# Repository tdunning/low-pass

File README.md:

# 5th Order Chebyshev Low Pass Filter

This directory contains the design for a low-pass filter designed with
anti-aliasing in mind and laid out to avoid inadvertent coupling.

A typical use might be on the output of a direct synthesis chip such
as the AD9851. The DAC in an AD9851 is clocked at 180Ms/s which gives
rise to sampling noise at 180MHz. In addition, if you are generating a
waveform at frequency $f$, there will be an image in frequency space
of that output at $180MHz - f$. This filter is intended to suppress
such unwanted signals.

The circuit here is designed for the specific case of sampling at
180MHz and allowing outputs up to 60Mhz, while suppressing undesirable
outputs by at least 60dB. One of the filter poles is specially
adjusted to fall directly on the sampling frequency for maximum
suppression.

The design is also tuned to give very flat response for an output
impedance of 50 Ω. With a 1kΩ load, the passband response of the
filter alone can show variations in insertion loss of up to 3dB. To
minimize that effect, a 200Ω pre-load resistor is included in the
design. The stopband is relatively insensitive to variations in load.

The primary design here is a 4-layer board in order to minimize the
distance from the signal-carrying traces to the closest ground
plane. The design works nearly as well with a 2-layer board, but there
is noticeable degradation in performance as shown in the image above.

# Licensing

This project is licensed under the MIT license with the idea that the 
circuit designs and layouts are simply a form of software.

Please share and enjoy if you build something cool based on this work.

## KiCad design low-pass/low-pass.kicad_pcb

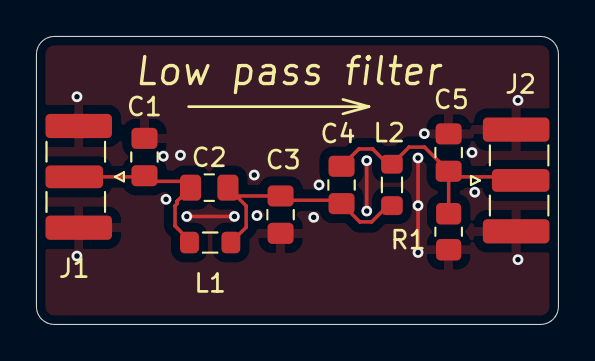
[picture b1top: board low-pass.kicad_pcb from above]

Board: 4 copper layers, 29.0 x 16.0 mm, 10 parts (0 on the bottom side), 4 nets.

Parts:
C1, C5: 82p; C_0805_2012Metric_Pad1.18x1.45mm_HandSolder
C2: 4.7p; C_0805_2012Metric_Pad1.18x1.45mm_HandSolder
C3: 120p; C_0805_2012Metric_Pad1.18x1.45mm_HandSolder
C4: 15p; C_0805_2012Metric_Pad1.18x1.45mm_HandSolder
J1, J2: Conn_Coaxial; SMA_Samtec_SMA-J-P-H-ST-EM1_EdgeMount
L1: 150n; L_0805_2012Metric_Pad1.05x1.20mm_HandSolder
L2: 120n; L_0805_2012Metric_Pad1.05x1.20mm_HandSolder
R1: 220; R_0805_2012Metric_Pad1.20x1.40mm_HandSolder

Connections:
GND: C1.2, C3.2, C5.2, J1.2 (Ext), J2.2 (Ext), R1.2
unnamed: C2.2, C3.1, C4.1, L1.2, L2.1
unnamed: C1.1, C2.1, J1.1 (In), L1.1
unnamed: C4.2, C5.1, J2.1 (In), L2.2, R1.1

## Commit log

2026-03-17 Cleaned up esthetics
2026-03-17 Added QR code to back
2026-03-29 Added two layer version and experimental results
2026-03-29 Updated README and fixed typo in analysis code
2026-03-29 Improved (I think) the two layer layout
2026-03-31 Create LICENSE
2026-03-31 Added comment on licensing
2026-04-02 Slight updates to the layout for possible improvement in isolation of components
